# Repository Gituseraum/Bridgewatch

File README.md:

# BridgeWatch - A Bridge Monitoring System

## Project Overview

Our project is a portable, non-invasive bridge monitoring system designed to continuously collect structural and environmental data. The device is housed in a weatherproof 3D-printed enclosure and can be attached to a bridge without drilling or permanently modifying the structure.

Using multiple sensors, the system measures bridge vibrations, environmental conditions, and traffic activity. A Raspberry Pi Pico processes the collected data and transmits it using LoRa to a nearby gateway. The gateway uploads the information to the cloud, where it can be viewed through a mobile application.

Rather than replacing professional bridge inspections, our device serves as an **early warning monitoring system**, helping engineers identify unusual changes in bridge behavior between routine inspections.

---

# Hardware

| Component | Purpose |
|-----------|---------|
| **Raspberry Pi Pico 2 (RP2350)** | Main controller that processes sensor data and communicates with the LoRa module. |
| **SX1276 LoRa Module** | Sends sensor data over long distances using very little power. |
| **ADXL355 High-Resolution Accelerometer** | Detects tiny bridge vibrations and changes in structural behavior. |
| **MPU-6050 Accelerometer & Gyroscope** | Measures larger movement, impacts, and orientation changes. |
| **BME280 Environmental Sensor** | Measures temperature, humidity, and atmospheric pressure. |
| **INMP441 MEMS Microphone** | Detects impacts and unusual acoustic events that may indicate structural anomalies. |

---
# Schematic

---
# Route

# Mobile App Features

## Dashboard

The dashboard provides a quick overview of the bridge's current condition.

### Features

- Bridge Health Score
- Bridge Status (Normal / Warning / Critical)
- Battery Level
- Current Traffic Level
- Last Data Update
- Active Alerts
- Quick Sensor Summary

## Live Monitoring

Displays live sensor readings in real time.

## Historical Data

Stores previous bridge data for long-term analysis.

---

# Why is this important?

Bridges are critical pieces of infrastructure that millions of people rely on every day. Most bridges are only inspected every few months or years, meaning structural changes that occur between inspections can go unnoticed.

Our project fills this gap by providing **continuous, real-time monitoring**. Instead of replacing professional inspections, the system acts as an **early warning tool**, detecting abnormal changes in vibration, movement, and environmental conditions that may indicate a developing problem.

By combining affordable sensors with long-range LoRa communication, this system offers a scalable and cost-effective solution that could be deployed on many bridges rather than only high-value infrastructure. Continuous monitoring allows engineers to observe how bridges respond to traffic, weather, and long-term wear while identifying trends that may require further investigation.

In addition to structural monitoring, the system also estimates traffic levels using vibration analysis. This information can help transportation departments understand bridge usage, identify heavily traveled routes, and make informed decisions about maintenance scheduling and future infrastructure improvements.

### Benefits

- Continuous bridge monitoring
- Early warning notifications
- Remote monitoring using LoRa
- Low-cost and scalable design
- Non-invasive installation
- Weather-resistant enclosure
- Historical data logging
- Traffic analysis
- Supports preventative maintenance
- Helps reduce inspection costs
- Improves infrastructure management

Plan:

Home Page:
Live bridge status
Historical Bridge Data List
Time, date, other cosmetic stuff

Sensor Page:
Sensor Stuff

About Us:
BridgeWatch Overview - scroll up

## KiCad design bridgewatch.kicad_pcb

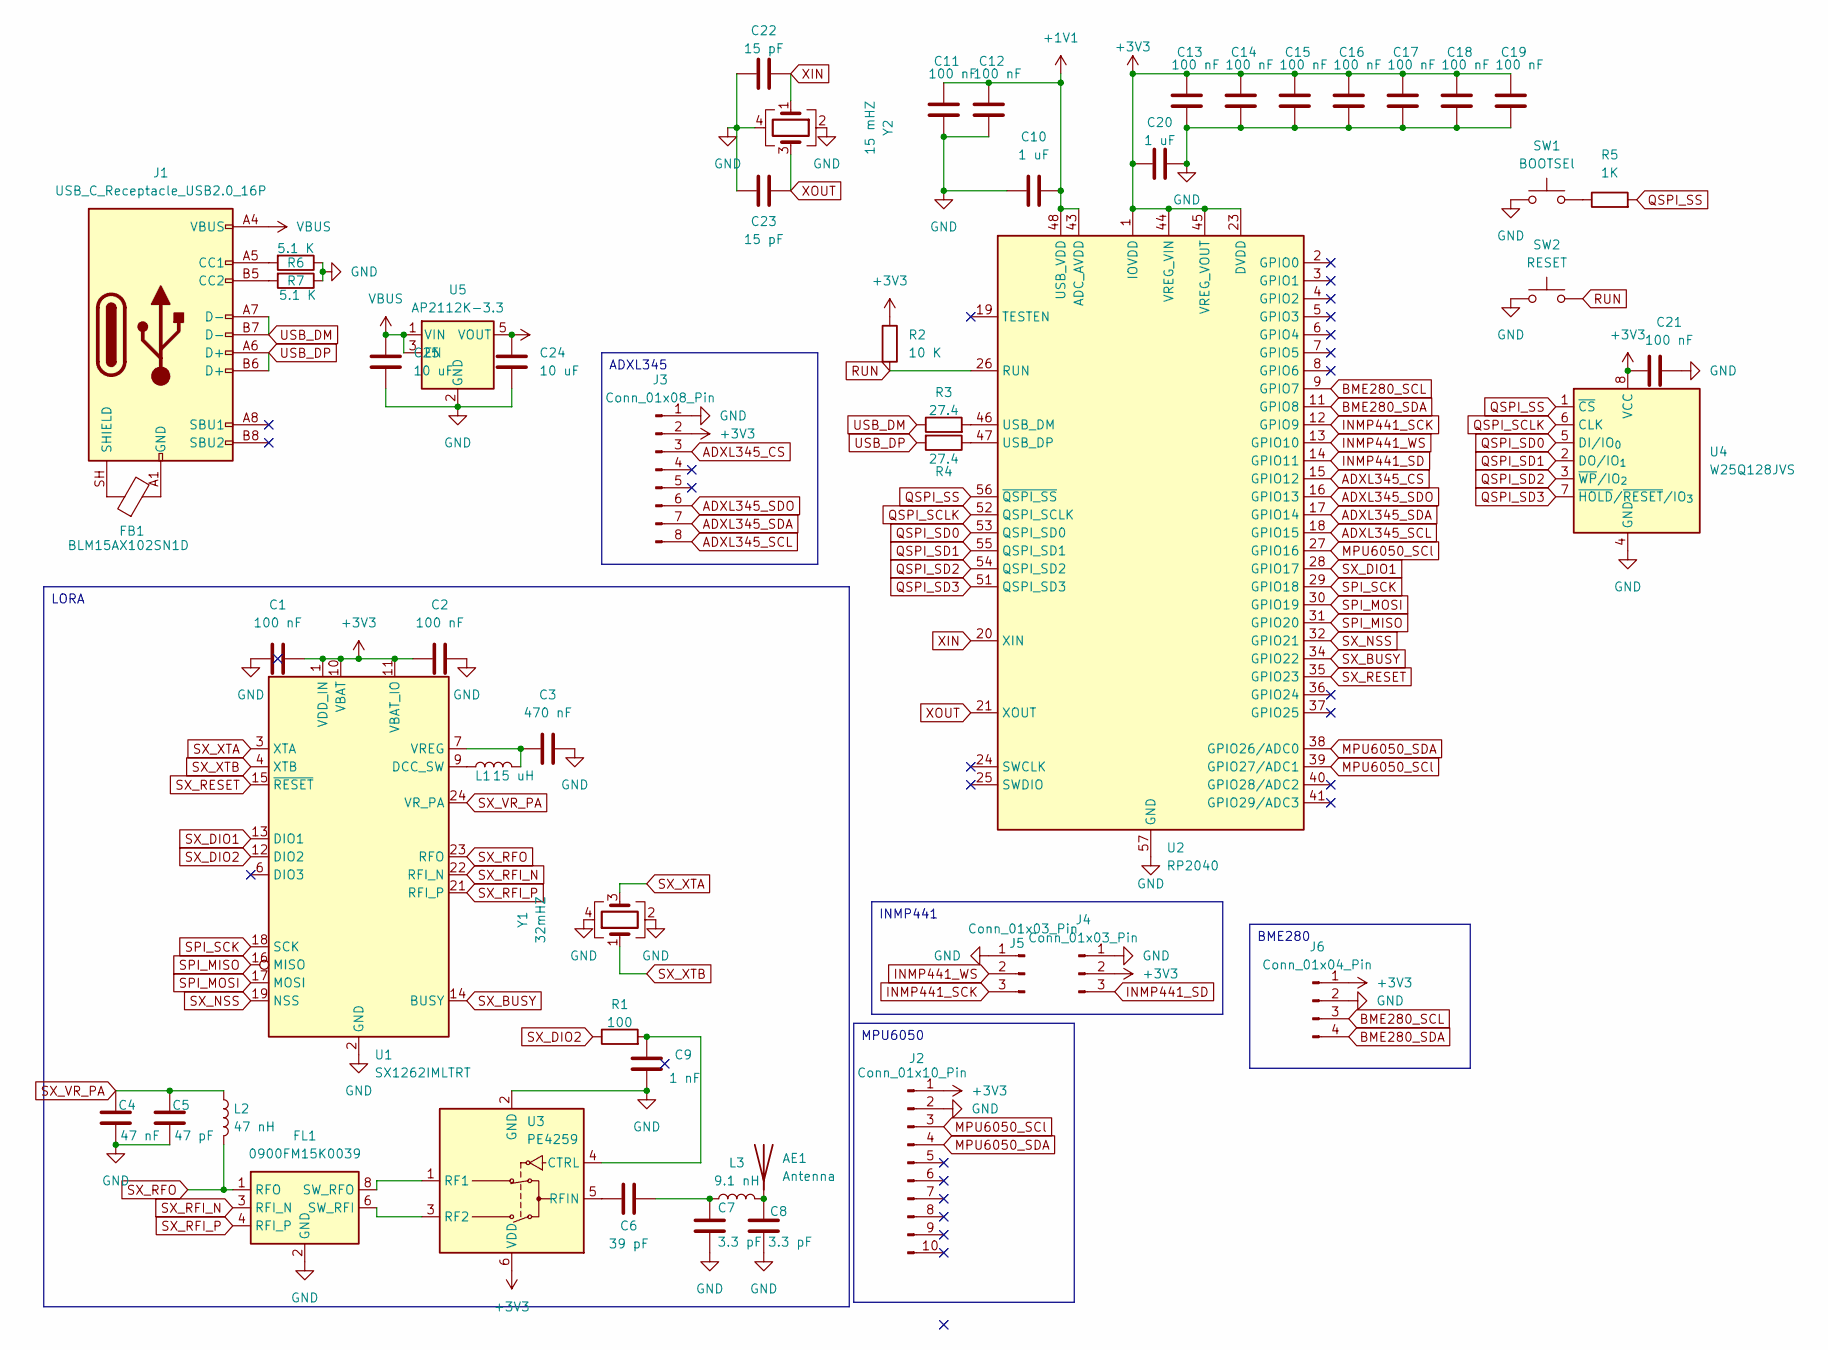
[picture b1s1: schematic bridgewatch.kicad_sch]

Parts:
AE1: Antenna; PinSocket_1x01_P2.54mm_Horizontal
C1, C2, C11, C12, C13, C14, C15, C16, C17, C18, C19, C21: 100 nF; C_0402_1005Metric
C3: 470 nF; C_0402_1005Metric
C4: 47 nF; C_0402_1005Metric
C5: 47 pF; C_0402_1005Metric
C6: 39 pF; C_0402_1005Metric
C7, C8: 3.3 pF; C_0402_1005Metric
C9: 1 nF; C_0402_1005Metric
C10, C20: 1 uF; C_0402_1005Metric
C22, C23: 15 pF; C_0402_1005Metric
C24, C25: 10 uF; C_0402_1005Metric
FB1: BLM15AX102SN1D; L_0402_1005Metric
FL1: 0900FM15K0039; Balun_Johanson_0900FM15K0039
J1: USB_C_Receptacle_USB2.0_16P; USB_C_Receptacle_GCT_USB4105-xx-A_16P_TopMnt_Horizontal
J2: Conn_01x10_Pin; PinSocket_1x10_P2.54mm_Vertical
J3: Conn_01x08_Pin; PinSocket_1x08_P2.54mm_Vertical
J4, J5: Conn_01x03_Pin; PinSocket_1x03_P2.54mm_Vertical
J6: Conn_01x04_Pin; PinSocket_1x04_P2.54mm_Vertical
L1: 15 uH; L_0402_1005Metric
L2: 47 nH; L_0402_1005Metric
L3: 9.1 nH; L_0402_1005Metric
R1: 100; R_0402_1005Metric
R2: 10 K; R_0402_1005Metric
R3, R4: 27.4; R_0402_1005Metric
R5: 1K; R_0402_1005Metric
R6, R7: 5.1 K; R_0402_1005Metric
SW1: BOOTSEl; SW_Tactile_SPST_NO_Straight_CK_PTS636Sx25SMTRLFS
SW2: RESET; SW_Tactile_SPST_NO_Straight_CK_PTS636Sx25SMTRLFS
U1: SX1262IMLTRT; QFN-24-1EP_4x4mm_P0.5mm_EP2.6x2.6mm
U2: RP2040; QFN-56-1EP_7x7mm_P0.4mm_EP3.2x3.2mm
U3: PE4259; SOT-363_SC-70-6
U4: W25Q128JVS; SOIC-8_5.3x5.3mm_P1.27mm
U5: AP2112K-3.3; SOT-23-5
Y1: 32mHZ; Crystal_SMD_3225-4Pin_3.2x2.5mm
Y2: 15 mHZ; Crystal_SMD_Abracon_ABM8G-4Pin_3.2x2.5mm

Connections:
+1V1: C10.2, C11.1, C12.1, U2.43 (ADC_AVDD), U2.48 (USB_VDD)
+3V3: C1.2, C2.1, C13.1, C14.1, C15.1, C16.1, C17.1, C18.1, C19.1, C20.1, C21.2, C24.1, J2.1, J3.2, J4.2, J6.1, R2.1, U1.1 (VDD_IN), U1.10 (VBAT), U1.11 (VBAT_IO), U2.1 (IOVDD), U2.10 (IOVDD), U2.22 (IOVDD), U2.23 (DVDD), U2.33 (IOVDD), U2.42 (IOVDD), U2.44 (VREG_VIN), U2.45 (VREG_VOUT), U2.49 (IOVDD), U2.50 (DVDD), U3.6 (VDD), U4.8 (VCC), U5.5 (VOUT)
ADXL345_CS: J3.3, U2.15 (GPIO12)
ADXL345_SCL: J3.8, U2.18 (GPIO15)
ADXL345_SDA: J3.7, U2.17 (GPIO14)
ADXL345_SDO: J3.6, U2.16 (GPIO13)
BME280_SCL: J6.3, U2.9 (GPIO7)
BME280_SDA: J6.4, U2.11 (GPIO8)
GND: C1.1, C2.2, C3.2, C4.2, C5.2, C7.2, C8.2, C9.2, C10.1, C11.2, C12.2, C13.2, C14.2, C15.2, C16.2, C17.2, C18.2, C19.2, C20.2, C21.1, C22.1, C23.1, C24.2, C25.2, FL1.2 (GND), FL1.5 (GND), FL1.7 (GND), FL1.9 (GND), FL1.10 (GND), J2.2, J3.1, J4.1, J5.1, J6.2, R6.1, R7.1, SW1.1, SW2.1, U1.2 (GND), U1.5 (GND), U1.8 (GND), U1.20 (GND), U1.25 (GND), U2.57 (GND), U3.2 (GND), U4.4 (GND), U5.2 (GND), Y1.2 (G), Y1.4 (G), Y2.2 (G), Y2.4 (G)
INMP441_SCK: J5.3, U2.12 (GPIO9)
INMP441_SD: J4.3, U2.14 (GPIO11)
INMP441_WS: J5.2, U2.13 (GPIO10)
MPU6050_SCl: J2.3, U2.27 (GPIO16), U2.39 (GPIO27/ADC1)
MPU6050_SDA: J2.4, U2.38 (GPIO26/ADC0)
unnamed: AE1.1 (A_1), C8.1, L3.2
unnamed: C6.1, C7.1, L3.1
unnamed: FB1.2, J1.A1 (GND), J1.A12 (GND), J1.B1 (GND), J1.B12 (GND)
unnamed: FL1.6 (SW_RFI), U3.3 (RF2)
unnamed: FL1.8 (SW_RFO), U3.1 (RF1)
unnamed: J1.A5 (CC1), R6.2
unnamed: J1.B5 (CC2), R7.2
unnamed: FB1.1, J1.SH (SHIELD)
unnamed: R5.1, SW1.2
unnamed: L1.1, U1.9 (DCC_SW)
unnamed: C3.1, L1.2, U1.7 (VREG)
unnamed: R3.2, U2.46 (USB_DM)
unnamed: R4.1, U2.47 (USB_DP)
unnamed: C9.1, R1.2, U3.4 (CTRL)
unnamed: C6.2, U3.5 (RFIN)
QSPI_SCLK: U2.52 (QSPI_SCLK), U4.6 (CLK)
QSPI_SD0: U2.53 (QSPI_SD0), U4.5 (DI/IO_{0})
QSPI_SD1: U2.55 (QSPI_SD1), U4.2 (DO/IO_{1})
QSPI_SD2: U2.54 (QSPI_SD2), U4.3 (~WP/IO_{2})
QSPI_SD3: U2.51 (QSPI_SD3), U4.7 (~HOLD/~RESET/IO_{3})
QSPI_SS: R5.2, U2.56 (~QSPI_SS), U4.1 (~CS)
RUN: R2.2, SW2.2, U2.26 (RUN)
SPI_MISO: U1.16 (MISO), U2.31 (GPIO20)
SPI_MOSI: U1.17 (MOSI), U2.30 (GPIO19)
SPI_SCK: U1.18 (SCK), U2.29 (GPIO18)
SX_BUSY: U1.14 (BUSY), U2.34 (GPIO22)
SX_DIO1: U1.13 (DIO1), U2.28 (GPIO17)
SX_DIO2: R1.1, U1.12 (DIO2)
SX_NSS: U1.19 (NSS), U2.32 (GPIO21)
SX_RESET: U1.15 (~RESET), U2.35 (GPIO23)
SX_RFI_N: FL1.3 (RFI_N), U1.22 (RFI_N)
SX_RFI_P: FL1.4 (RFI_P), U1.21 (RFI_P)
SX_RFO: FL1.1 (RFO), L2.2, U1.23 (RFO)
SX_VR_PA: C4.1, C5.1, L2.1, U1.24 (VR_PA)
SX_XTA: U1.3 (XTA), Y1.3
SX_XTB: U1.4 (XTB), Y1.1
USB_DM: J1.A7 (D-), J1.B7 (D-), R3.1
USB_DP: J1.A6 (D+), J1.B6 (D+), R4.2
VBUS: C25.1, J1.A4 (VBUS), J1.A9 (VBUS), J1.B4 (VBUS), J1.B9 (VBUS), U5.1 (VIN), U5.3 (EN)
XIN: C22.2, U2.20 (XIN), Y2.1
XOUT: C23.2, U2.21 (XOUT), Y2.3

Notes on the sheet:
MPU6050
BME280
INMP441
ADXL345
LORA

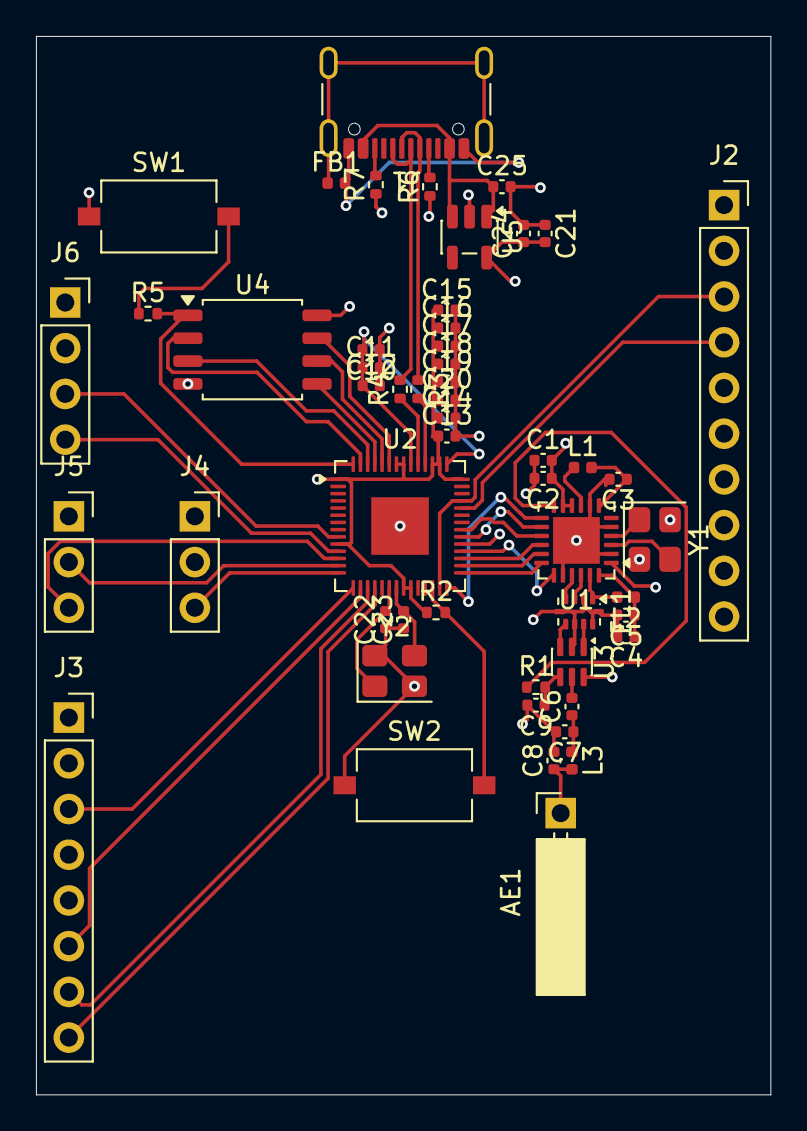
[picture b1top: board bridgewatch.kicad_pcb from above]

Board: 4 copper layers, 40.8 x 58.8 mm, 53 parts (0 on the bottom side), 55 nets.
